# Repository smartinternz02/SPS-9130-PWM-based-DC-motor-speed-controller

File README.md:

# SPS-9130-PWM-based-DC-motor-speed-controller
PWM based DC motor speed controller
This project contains document of DC motor controller,demo video,schematic and PCB screenshots and gerber files.Created using Eagle software.

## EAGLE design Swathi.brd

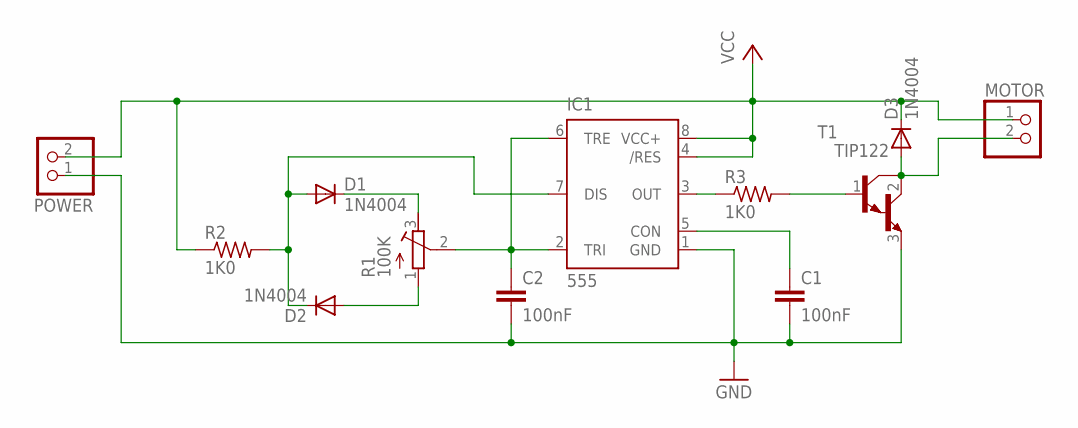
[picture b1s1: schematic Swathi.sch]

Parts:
C1, C2: 100nF; C025-025X050
D1, D2, D3: 1N4004; DO41-10
IC1: 555; DIP08
MOTOR: PINHD-1X2; 1X02
POWER: PINHD-1X2; 1X02
R1: 100K; RTRIM64W
R2, R3: 1K0; 0204/7
T1: TIP122; TO220

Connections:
GND: C1.2, C2.2, IC1.1 (GND), POWER.1, T1.3 (E)
unnamed: C2.1, IC1.2 (TRI), IC1.6 (TRE), R1.2 (S)
unnamed: C1.1, IC1.5 (CON)
unnamed: D1.C, R1.3 (E)
unnamed: D2.A, R1.1 (A)
unnamed: D1.A, D2.C, IC1.7 (DIS), R2.2
unnamed: IC1.3 (OUT), R3.1
unnamed: R3.2, T1.1 (B)
unnamed: D3.A, MOTOR.2, T1.2 (C)
VCC: D3.C, IC1.4 (/RES), IC1.8 (VCC+), MOTOR.1, POWER.2, R2.1

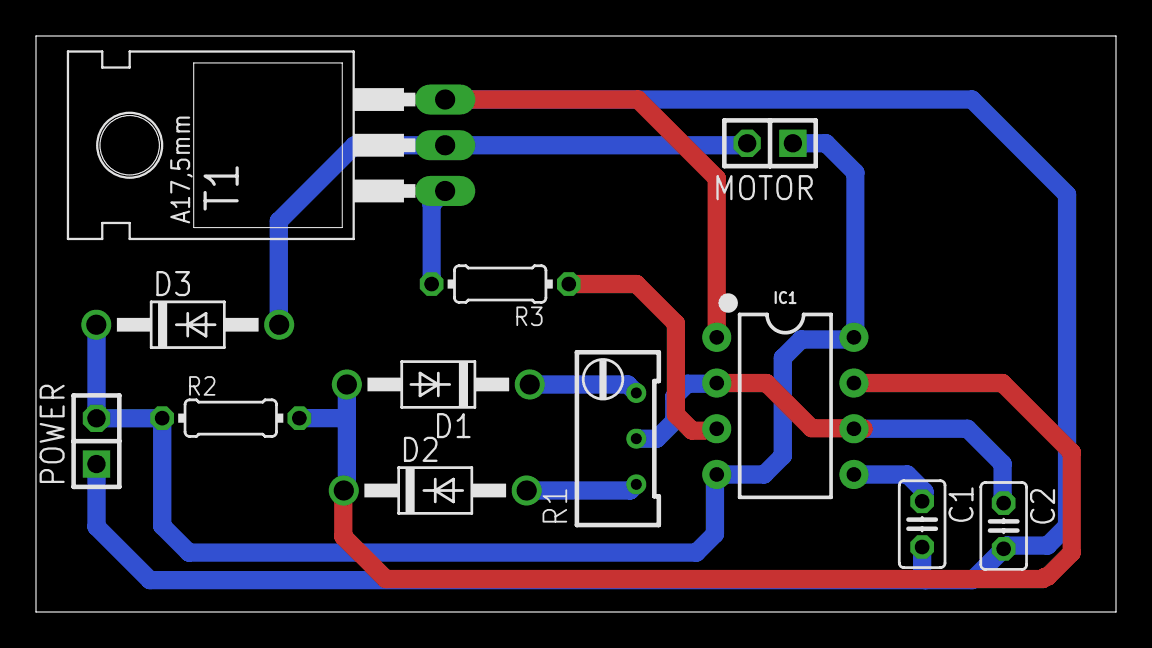
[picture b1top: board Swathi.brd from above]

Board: 2 copper layers, 60.0 x 32.0 mm, 12 parts (0 on the bottom side), 10 nets.

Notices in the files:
parts and their libraries:
SparkFun-IC-Special-Function: Licensing: Creative Commons ShareAlike 4.0 International - https://creativecommons.org/licenses/by-sa/4.0
